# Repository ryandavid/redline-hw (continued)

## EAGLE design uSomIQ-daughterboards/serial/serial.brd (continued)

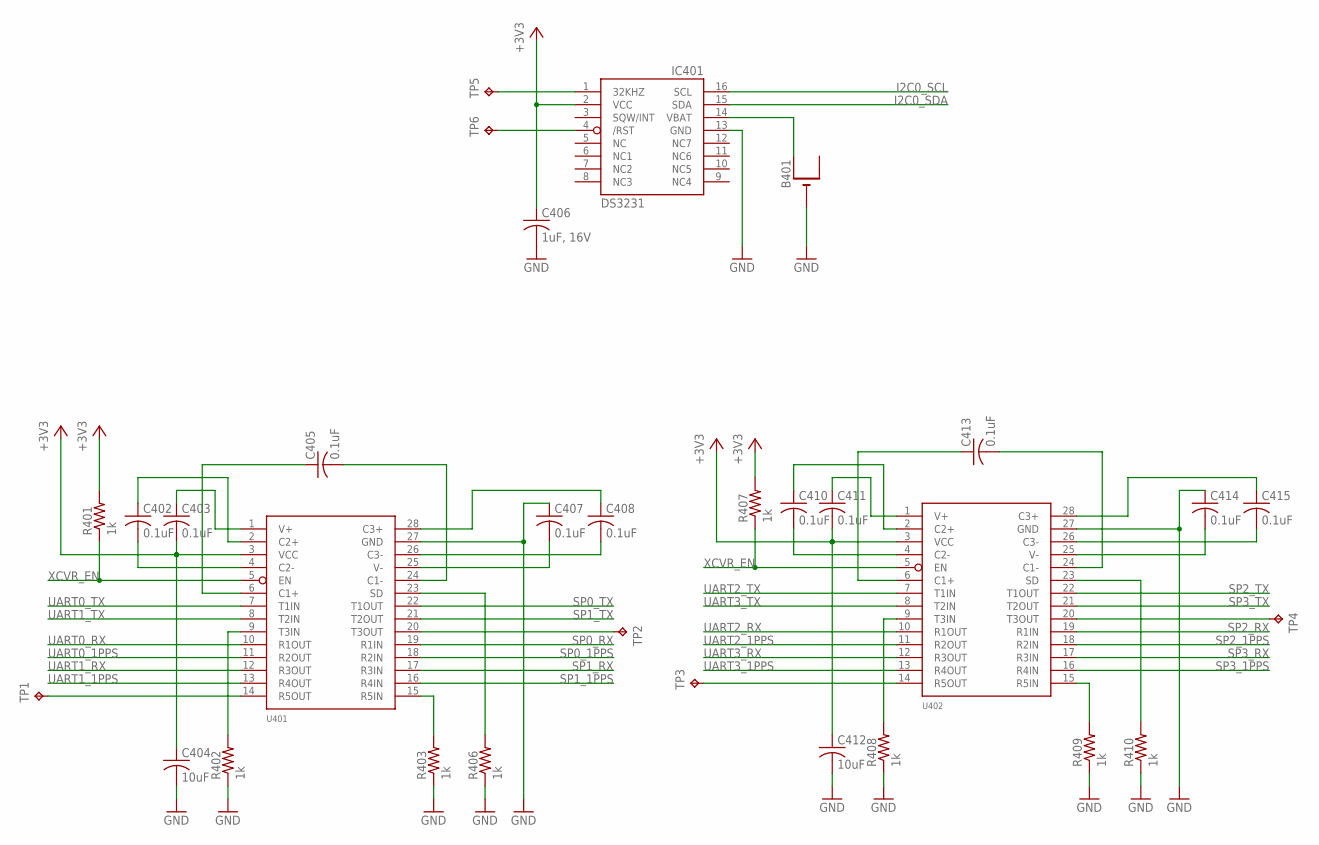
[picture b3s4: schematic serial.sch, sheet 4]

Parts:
B401: CR1220THM; CR1220-THM
C402, C403, C405, C407, C408, C410, C411, C413, C414, C415: 0.1uF; C0603
C404, C412: 10uF; C0603
C406: 1uF, 16V; C0603
IC401: DS3231/SO; SO16W
R401, R402, R403, R406, R407, R408, R409, R410: 1k; R0603
TP1, TP2, TP3, TP4, TP5, TP6: TPB1,27; B1,27
U401, U402: ADM3311E; TSSOP28

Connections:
+3V3: C403.2, C404.1, C406.1, C411.2, C412.1, IC401.2 (VCC), R401.2, R407.2, U401.3 (VCC), U402.3 (VCC); also elsewhere on the board
GND: B401.-, C404.2, C406.2, C407.1, C412.2, C414.1, IC401.13 (GND), R402.1, R403.1, R406.1, R408.1, R409.1, R410.1, U401.27 (GND), U402.27 (GND); also elsewhere on the board
I2C0_SCL: IC401.16 (SCL); also elsewhere on the board
I2C0_SDA: IC401.15 (SDA); also elsewhere on the board
unnamed: IC401.1 (32KHZ), TP5.TP
unnamed: B401.+1 (+), IC401.14 (VBAT)
unnamed: C403.1, U401.1 (V+)
unnamed: C411.1, U402.1 (V+)
unnamed: C402.1, U401.2 (C2+)
unnamed: C402.2, U401.4 (C2-)
unnamed: R402.2, U401.9 (T3IN)
unnamed: TP1.TP, U401.14 (R5OUT)
unnamed: TP2.TP, U401.20 (T3OUT)
unnamed: R403.2, U401.15 (R5IN)
unnamed: R406.2, U401.23 (SD)
unnamed: C405.1, U401.6 (C1+)
unnamed: C405.2, U401.24 (C1-)
unnamed: C407.2, U401.25 (V-)
unnamed: C410.1, U402.2 (C2+)
unnamed: C408.2, U401.26 (C3-)
unnamed: C408.1, U401.28 (C3+)
unnamed: C410.2, U402.4 (C2-)
unnamed: R408.2, U402.9 (T3IN)
unnamed: TP3.TP, U402.14 (R5OUT)
unnamed: TP4.TP, U402.20 (T3OUT)
unnamed: R409.2, U402.15 (R5IN)
unnamed: R410.2, U402.23 (SD)
unnamed: C413.1, U402.6 (C1+)
unnamed: C413.2, U402.24 (C1-)
unnamed: C414.2, U402.25 (V-)
unnamed: C415.2, U402.26 (C3-)
unnamed: C415.1, U402.28 (C3+)
unnamed: IC401.4 (/RST), TP6.TP
SP0_1PPS: U401.18 (R2IN); also elsewhere on the board
SP0_RX: U401.19 (R1IN); also elsewhere on the board
SP0_TX: U401.22 (T1OUT); also elsewhere on the board
SP1_1PPS: U401.16 (R4IN); also elsewhere on the board
SP1_RX: U401.17 (R3IN); also elsewhere on the board
SP1_TX: U401.21 (T2OUT); also elsewhere on the board
SP2_1PPS: U402.18 (R2IN); also elsewhere on the board
SP2_RX: U402.19 (R1IN); also elsewhere on the board
SP2_TX: U402.22 (T1OUT); also elsewhere on the board
SP3_1PPS: U402.16 (R4IN); also elsewhere on the board
SP3_RX: U402.17 (R3IN); also elsewhere on the board
SP3_TX: U402.21 (T2OUT); also elsewhere on the board
UART0_1PPS: U401.11 (R2OUT); also elsewhere on the board
UART0_RX: U401.10 (R1OUT); also elsewhere on the board
UART0_TX: U401.7 (T1IN); also elsewhere on the board
UART1_1PPS: U401.13 (R4OUT); also elsewhere on the board
UART1_RX: U401.12 (R3OUT); also elsewhere on the board
UART1_TX: U401.8 (T2IN); also elsewhere on the board
UART2_1PPS: U402.11 (R2OUT); also elsewhere on the board
UART2_RX: U402.10 (R1OUT); also elsewhere on the board
UART2_TX: U402.7 (T1IN); also elsewhere on the board
UART3_1PPS: U402.13 (R4OUT); also elsewhere on the board
UART3_RX: U402.12 (R3OUT); also elsewhere on the board
UART3_TX: U402.8 (T2IN); also elsewhere on the board
XCVR_EN: R401.1, R407.1, U401.5 (EN), U402.5 (EN)

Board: 2 copper layers, 72 parts (0 on the bottom side), 86 nets, no tracks yet.

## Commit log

2015-07-28 Add uSomIQ-AM334x to library
2015-08-05 Add power supply and RTC
2015-08-20 Add Molex Mini-D connector to library
2015-08-21 Add initial pinout for baseboards
2015-08-24 Add serial port connectors
2015-08-28 Update baseboard pinouts
2015-09-01 Add RS232 transcievers
2015-09-02 Update libraries, add power supply monitoring
2015-09-04 Start to place serial daughterboard power supply
2015-09-14 Initial part placement for serial daughterboard
2016-05-12 Redesign ADS-B receiver schem for ODROID-C2
2016-05-16 Updates from first schem review
2016-05-17 basic floorplanning. redefined the origin-area as the shape ryan drew elsewhere. moved all the stuffs into the new board. laid out components to be in logical groups. to-do: begin defining power/grou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
2016-05-18 agile as a motherfucker. added a few 5V power traces. connected a few things to a few other things. incremental.
2016-05-19 Fix ODROID-C2 board outline, add pull-ups for FETs
2016-05-20 ADS-B board sloppily laid out
